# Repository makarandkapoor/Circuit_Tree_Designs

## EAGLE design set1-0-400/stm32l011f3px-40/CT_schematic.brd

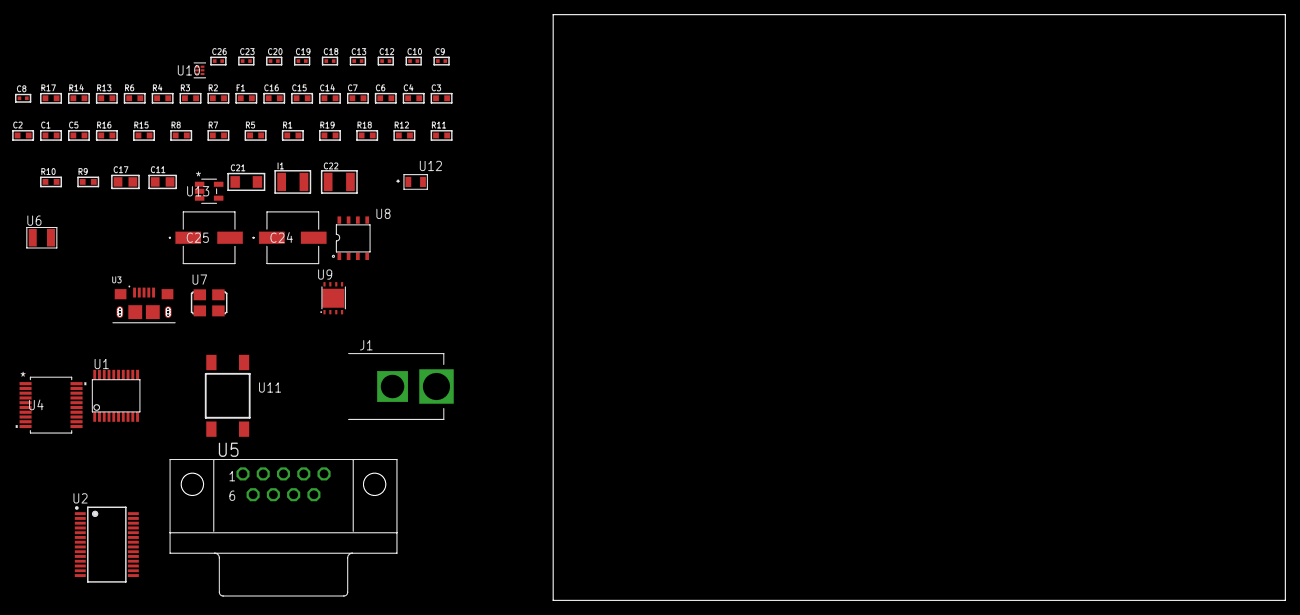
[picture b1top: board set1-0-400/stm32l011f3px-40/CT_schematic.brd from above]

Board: 2 copper layers, 61 parts (0 on the bottom side), 46 nets, no tracks yet.

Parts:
C1, C2, C3, C4: 1e-07; C0603
C5: 4.7e-06; C0603
C6: 1e-08; C0603
C7, C14, C15, C16: 1e-06; C0603
C8, C9: 1e-11; C0402
C10, C12, C13, C23: 1e-07; C0402
C11, C17: 4.7e-06; C0805
C18, C19, C20, C26: 1e-08; C0402
C21: 1e-05; C1206
C22: 1e-05; C1210
C24, C25: 0.0001; EXV-9H
F1: 240.0; L0603
I1: 1.5e-05; L1210
J1: PJ-037B; PJ-037B_PACKAGE
R1, R5, R7, R8, R15, R16: 10000.0; R0603
R2, R14: 1000.0; R0603
R3: 1600.5; R0603
R4, R6: 4700.0; R0603
R9, R10, R11, R12: 100000.0; R0603
R13: 2231.0; R0603
R17: 9100.0; R0603
R18: 680000.0; R0603
R19: 120000.0; R0603
U1: STM32L011F3P6; TSSOP20-I
U2: FT232RL-REEL; SSOP-28
U3: 10118193-0001LF; FCI_10118193-0001LF
U4: MAX3218EAP+T; SSOP-20
U5: 182-009-113R531; 182-009-MALE
U6: ABS07-32.768KHZ-7-T
U7: ASFL1-12MHZ-NCS; ASFL1
U8: idt74fct38072; IDT74FCT38072
U9: LP3878SDX-ADJ/NOPB; WSON-8
U10: TPS3895ADRYR; SON-6
U11: 4-1437565-2; SW_4-1437565-2
U12: Q65110A2395; LGM67K-G1J2-24-Z
U13: nc7sz125m5x; NC7SZ125M5X

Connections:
CLK_CRYSTAL_U1_2: C8.1, U1.2, U6.1
CLK_CRYSTAL_U1_3: C9.1, U1.3, U6.2
CLK_U1_6: U1.6, U8.7
CLK_U2_27: U2.27, U8.6
CLK_U8_3: U7.3, U8.3
GND: C1.2, C2.2, C3.2, C4.2, C5.2, C6.2, C7.2, C8.2, C9.2, C10.2, C11.2, C12.2, C13.2, C14.2, C15.2, C16.2, C18.2, C19.2, C20.2, C21.2, C22.2, C23.2, C24.2, C25.2, C26.2, J1.2, R2.2, R5.2, R8.2, R14.2, R17.2, R19.2, U1.15, U2.7, U2.18, U2.21, U2.25, U2.26, U3.5, U3.6, U3.7, U3.8, U3.9, U4.5, U4.17, U4.20, U5.5, U7.2, U8.4, U8.5, U8.8, U9.3, U9.PAD, U10.2, U12.C, U13.1, U13.3
NET_U1_1: R5.1, U1.1
NET_U1_4: R4.1, U1.4, U13.4
NET_U1_5: C6.1, C7.1, F1.1, U1.5
NET_U1_19: R3.1, U1.19, U12.A
NET_U1_20: R1.1, U1.20, U11.3, U11.4
NET_U2_14: R7.1, U2.14
NET_U2_17: C12.1, U2.17
NET_U2_19: R8.1, U2.19
NET_U3_1: R6.1, U3.1
NET_U3_2: U2.16, U3.2
NET_U3_3: U2.15, U3.3
NET_U4_1: I1.1, U4.1
NET_U4_2: R9.1, U4.2
NET_U4_3: R10.1, U4.3
NET_U4_4: R11.1, U4.4
NET_U4_15: C16.1, U4.15
NET_U4_16: C17.2, U4.16
NET_U4_18: C17.1, U4.18
NET_U4_19: C15.1, U4.19
NET_U5_2: U4.12, U5.2
NET_U5_3: U4.14, U5.3
NET_U5_7: U4.11, U5.7
NET_U5_8: U4.13, U5.8
NET_U9_1: C20.1, U9.1
NET_U9_6: R13.2, R14.1, U9.6
NET_U9_8: R12.1, U9.8
NET_U10_1: R16.1, R17.1, U10.1
NET_U10_3: R18.2, R19.1, U10.3
NET_U10_4: R15.1, U10.4, U13.2
NET_U11_1: R2.1, U11.1, U11.2
PROC_LPUART1_CTS: U1.12, U4.8
PROC_LPUART1_RTS: U1.14, U4.10
PROC_LPUART1_RX: U1.9, U4.9
PROC_LPUART1_TX: U1.8, U4.7
PROC_USART2_CTS: U1.13, U2.3
PROC_USART2_RTS: U1.7, U2.11
PROC_USART2_RX: U1.18, U2.1
PROC_USART2_TX: U1.17, U2.5
VCC_S1_10V1: C21.1, C24.1, C25.1, J1.1, R12.2, U9.4
VCC_TIER1_3V3: C1.1, C2.1, C3.1, C4.1, C5.1, C10.1, C11.1, C13.1, C14.1, C18.1, C19.1, C22.1, C23.1, C26.1, F1.2, I1.2, R1.2, R3.2, R4.2, R7.2, R9.2, R10.2, R11.2, R13.1, R15.2, R16.2, R18.1, U1.16, U2.4, U2.20, U4.6, U7.4, U8.1, U8.2, U9.5, U10.6, U13.5

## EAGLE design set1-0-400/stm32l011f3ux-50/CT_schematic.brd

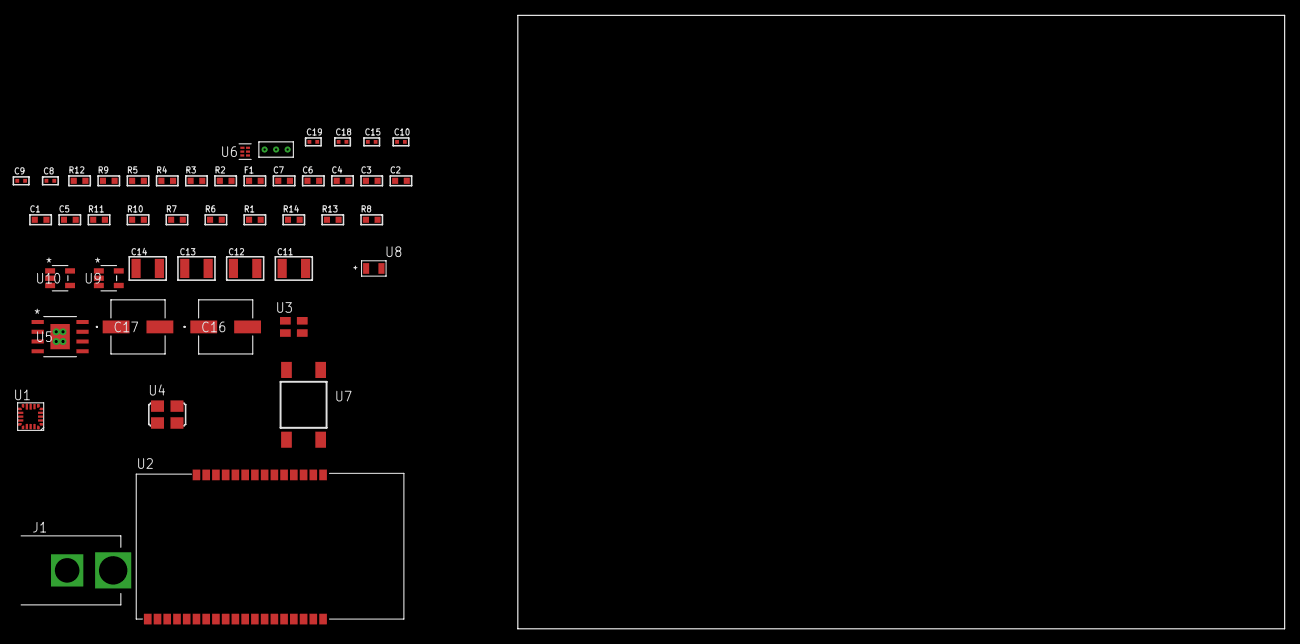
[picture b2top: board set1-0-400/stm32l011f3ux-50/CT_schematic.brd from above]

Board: 2 copper layers, 100.0 x 80.0 mm, 46 parts (0 on the bottom side), 21 nets, no tracks yet.

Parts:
C1, C2, C3, C4: 1e-07; C0603
C5: 4.7e-06; C0603
C6: 1e-08; C0603
C7: 1e-06; C0603
C8, C15: 1e-07; C0402
C9, C10, C18, C19: 1e-08; C0402
C11, C12, C13, C14: 1e-05; C1210
C16, C17: 0.0001; EXV-9H
F1: 240.0; L0603
J1: PJ-037B; PJ-037B_PACKAGE
R1, R6, R7, R10, R11: 10000.0; R0603
R2: 1000.0; R0603
R3: 1600.5; R0603
R4, R5: 4700.0; R0603
R8: 4031.5447154472; R0603
R9: 2200.0; R0603
R12: 9100.0; R0603
R13: 680000.0; R0603
R14: 120000.0; R0603
U1: STM32L011F3U6TR; UFQFPN20
U2: ETRX3587
U3: ASEK-32.768KHz-ECST; ASEK
U4: ASFL1-12MHZ-NCS; ASFL1
U5: MIC5234YME; SOIC-8_EP
U6: TPS3895ADRYR; SON-6
U7: 4-1437565-2; SW_4-1437565-2
U8: Q65110A2395; LGM67K-G1J2-24-Z
U9, U10: nc7sz125m5x; NC7SZ125M5X
U11: Dummy; DUMMY_PACKAGE_92

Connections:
CLK_U1_1: U1.1, U3.3
CLK_U1_5: U1.5, U4.3
GND: C1.2, C2.2, C3.2, C4.2, C5.2, C6.2, C7.2, C8.2, C9.2, C10.2, C11.2, C12.2, C13.2, C14.2, C15.2, C16.2, C17.2, C18.2, C19.2, J1.2, R2.2, R6.2, R7.2, R9.2, R12.2, R14.2, U1.12, U2.1, U2.13, U2.19, U2.20, U2.31, U2.33, U3.2, U4.2, U5.7, U5.EPAD, U6.2, U8.C, U9.1, U9.3, U10.1, U10.3, U11.1
NET_U1_3: R5.1, U1.3, U10.4
NET_U1_4: C6.1, C7.1, F1.1, U1.4
NET_U1_19: R3.1, U1.19, U8.A
NET_U1_20: R1.1, R6.1, U1.20, U7.3, U7.4
NET_U2_7: R4.1, U2.7, U9.4
NET_U2_21: R7.1, U2.21
NET_U5_4: R8.2, R9.1, U5.4
NET_U6_1: R11.1, R12.1, U6.1
NET_U6_3: R13.2, R14.1, U6.3
NET_U6_4: R10.1, U6.4, U9.2, U10.2
NET_U7_1: R2.1, U7.1, U7.2
PROC_LPUART1_CTS: U1.9, U2.8
PROC_LPUART1_RTS: U1.11, U2.6
PROC_LPUART1_RX: U1.16, U2.17
PROC_LPUART1_TX: U1.6, U2.18
PROC_TIM2_CH3: U1.15, U11.2, U11.3
VCC_S1_15V6: C11.1, C12.1, C16.1, C17.1, J1.1, U5.5, U5.8
VCC_TIER1_3V3: C1.1, C2.1, C3.1, C4.1, C5.1, C8.1, C9.1, C10.1, C13.1, C14.1, C15.1, C18.1, C19.1, F1.2, R1.2, R3.2, R4.2, R5.2, R8.1, R10.2, R11.2, R13.1, U1.13, U2.32, U3.4, U4.4, U5.1, U6.6, U9.5, U10.5

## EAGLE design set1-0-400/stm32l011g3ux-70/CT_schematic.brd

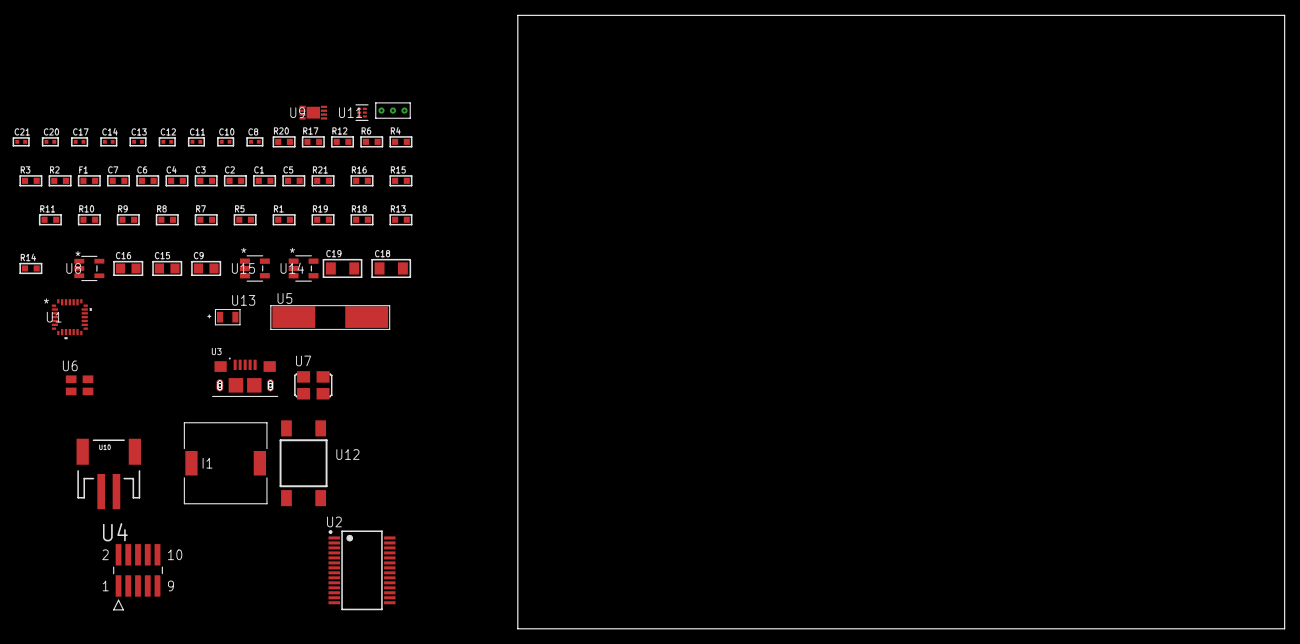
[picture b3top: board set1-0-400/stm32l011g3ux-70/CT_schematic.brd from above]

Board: 2 copper layers, 60 parts (0 on the bottom side), 37 nets, no tracks yet.

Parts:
C1, C2, C3, C4: 1e-07; C0603
C5: 4.7e-06; C0603
C6: 1e-08; C0603
C7: 1e-06; C0603
C8, C10, C11, C12, C17: 1e-07; C0402
C9: 4.7e-06; C0805
C13, C14, C20, C21: 1e-08; C0402
C15, C16: 1e-05; C0805
C18, C19: 1e-05; C1206
F1: 240.0; L0603
I1: 2.5e-06; DR1040
R1, R5, R7, R8, R9, R10, R11, R15, R16, R21: 10000.0; R0603
R2: 1000.0; R0603
R3: 1600.5; R0603
R4, R6: 4700.0; R0603
R12: 5.0; R0603
R13: 220000.0; R0603
R14: 1000000.0; R0603
R17: 9100.0; R0603
R18: 680000.0; R0603
R19: 120000.0; R0603
R20: 2000.0; R0603
U1: STM32L011G3U6; UFQFPN28
U2: FT232RL-REEL; SSOP-28
U3: 10118193-0001LF; FCI_10118193-0001LF
U4: FTSH-105-01-L-DV-K; SAMTEC_FTSH-105-01-L-DV-K
U5: ABLS-12.000MHZ-B4-T
U6: ASEK-32.768KHz-ECST; ASEK
U7: ASFL1-12MHZ-NCS; ASFL1
U8: ltc3406es5; TSOT-23-5
U9: MCP73831T-2ACI/MC; DFN8_2X3MC
U10: S2B-PH-SM4-TB(LF)(SN); JST-2-SMD
U11: TPS3895ADRYR; SON-6
U12: 4-1437565-2; SW_4-1437565-2
U13: Q65110A2395; LGM67K-G1J2-24-Z
U14, U15: nc7sz125m5x; NC7SZ125M5X
U16: Dummy; DUMMY_PACKAGE_125

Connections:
CLK_CRYSTAL_U2_27: U2.27, U5.1
CLK_CRYSTAL_U2_28: U2.28, U5.2
CLK_U1_2: U1.2, U6.3
CLK_U1_6: U1.6, U7.3
GND: C1.2, C2.2, C3.2, C4.2, C5.2, C6.2, C7.2, C8.2, C9.2, C10.2, C11.2, C12.2, C13.2, C14.2, C15.2, C16.1, C16.2, C17.2, C18.2, C19.2, C20.2, C21.2, R2.2, R5.2, R8.2, R12.2, R13.2, R17.2, R19.2, R20.2, U1.16, U2.7, U2.18, U2.21, U2.25, U2.26, U3.5, U3.6, U3.7, U3.8, U3.9, U4.3, U4.5, U6.2, U7.2, U8.2, U9.6, U9.9, U10.2, U11.2, U13.C, U14.2, U14.3, U15.1, U15.3, U16.1
INPUT_USBPOWER_5V: C18.1, R6.1, R21.2, U3.1, U9.1, U9.2
NET_U1_1: R5.1, U1.1
NET_U1_4: R4.1, U1.4, U15.4
NET_U1_5: C6.1, C7.1, F1.1, U1.5
NET_U1_27: R3.1, U1.27, U13.A
NET_U1_28: R1.1, U1.28, U12.3, U12.4
NET_U2_14: R7.1, U2.14
NET_U2_17: C10.1, U2.17
NET_U2_19: R8.1, U2.19
NET_U3_2: U2.16, U3.2
NET_U3_3: U2.15, U3.3
NET_U4_9: R12.1, U4.9
NET_U8_3: I1.1, U8.3
NET_U8_5: R13.1, R14.1, U8.5
NET_U8_ATNET_3: I1.2, R14.2
NET_U9_5: R21.1, U9.5
NET_U9_8: R20.1, U9.8
NET_U11_1: R16.1, R17.1, U11.1
NET_U11_3: R18.2, R19.1, U11.3
NET_U11_4: R15.1, U11.4, U14.4, U15.2
NET_U12_1: R2.1, U12.1, U12.2
PROC_ADC_IN4: U1.10, U16.2
PROC_ADC_IN7: U1.13, U16.3
PROC_LPUART1_CTS: U1.12, U2.3
PROC_LPUART1_RTS: U1.15, U2.11
PROC_LPUART1_RX: U1.9, U2.1
PROC_LPUART1_TX: U1.7, U2.5
PROC_SYS_SWCLK: R10.1, U1.22, U4.4
PROC_SYS_SWDIO: R11.1, U1.21, U4.2
RST_OUT_U4_JTAG_RST_B: R9.1, U4.10, U14.1
VCC_S1_3V7: C15.1, C19.1, U8.4, U9.3, U9.4, U10.1
VCC_TIER1_3V3: C1.1, C2.1, C3.1, C4.1, C5.1, C8.1, C9.1, C11.1, C12.1, C13.1, C14.1, C16.2, C17.1, C20.1, C21.1, F1.2, I1.2, R1.2, R3.2, R4.2, R7.2, R9.2, R10.2, R11.2, R14.2, R15.2, R16.2, R18.1, U1.17, U2.4, U2.20, U4.1, U6.4, U7.4, U11.6, U14.5, U15.5

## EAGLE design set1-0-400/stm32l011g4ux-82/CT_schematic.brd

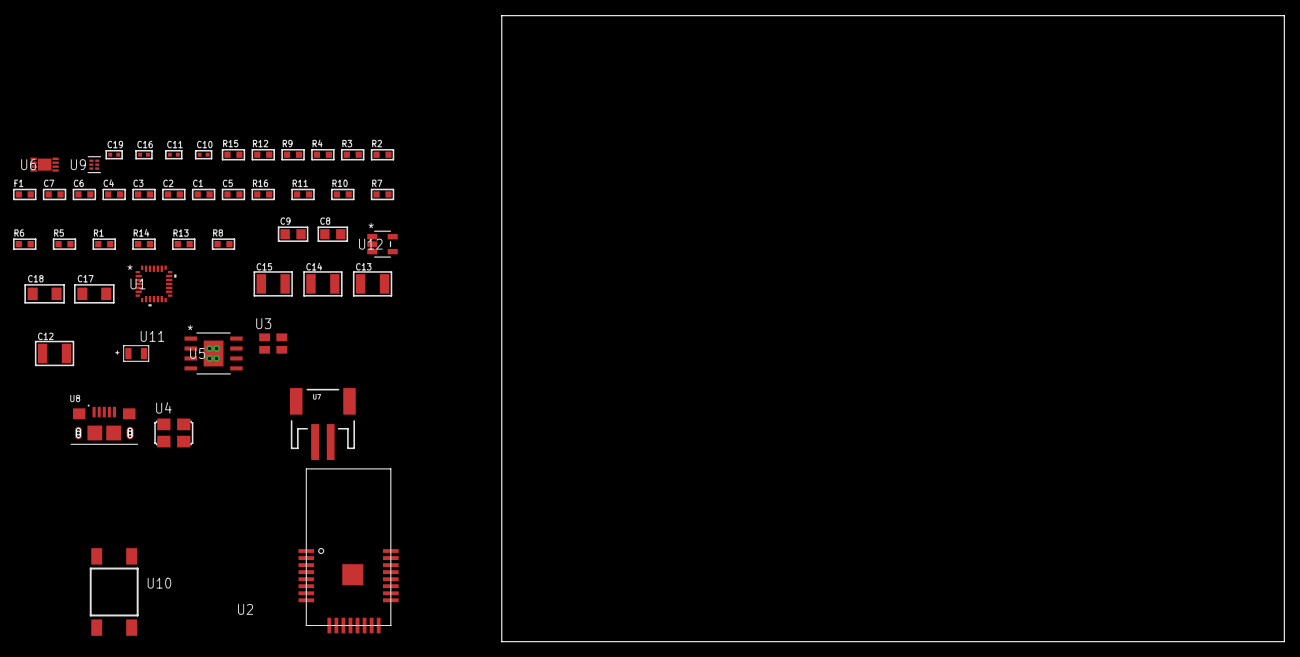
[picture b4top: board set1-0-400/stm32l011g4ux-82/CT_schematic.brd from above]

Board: 2 copper layers, 154.3 x 80.0 mm, 48 parts (0 on the bottom side), 24 nets, no tracks yet.

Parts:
C1, C2, C3, C4: 1e-07; C0603
C5: 4.7e-06; C0603
C6: 1e-08; C0603
C7: 1e-06; C0603
C8, C9: 1e-05; C0805
C10, C11, C19: 1e-08; C0402
C12, C13, C14, C15: 1e-05; C1210
C16: 1e-07; C0402
C17, C18: 1e-05; C1206
F1: 240.0; L0603
R1, R5, R6, R7, R10, R11, R16: 10000.0; R0603
R2: 1000.0; R0603
R3: 1600.5; R0603
R4: 4700.0; R0603
R8: 4031.5447154472; R0603
R9: 2200.0; R0603
R12: 9100.0; R0603
R13: 680000.0; R0603
R14: 120000.0; R0603
R15: 2000.0; R0603
U1: STM32L011G4U6; UFQFPN28
U2: ATBTLC1000-MR110CA
U3: ASEK-32.768KHz-ECST; ASEK
U4: ASFL1-12MHZ-NCS; ASFL1
U5: MIC5234YME; SOIC-8_EP
U6: MCP73831T-2ACI/MC; DFN8_2X3MC
U7: S2B-PH-SM4-TB(LF)(SN); JST-2-SMD
U8: 10118193-0001LF; FCI_10118193-0001LF
U9: TPS3895ADRYR; SON-6
U10: 4-1437565-2; SW_4-1437565-2
U11: Q65110A2395; LGM67K-G1J2-24-Z
U12: nc7sz125m5x; NC7SZ125M5X

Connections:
CLK_U1_2: U1.2, U3.3
CLK_U1_6: U1.6, U4.3
GND: C1.2, C2.2, C3.2, C4.2, C5.2, C6.2, C7.2, C8.2, C9.2, C10.2, C11.2, C12.2, C13.2, C14.2, C15.2, C16.2, C17.2, C18.2, C19.2, R2.2, R5.2, R9.2, R12.2, R14.2, R15.2, U1.16, U2.1, U2.9, U2.13, U2.24, U2.25, U3.2, U4.2, U5.7, U5.EPAD, U6.6, U6.9, U7.2, U8.5, U8.6, U8.7, U8.8, U8.9, U9.2, U11.C, U12.1, U12.3
INPUT_USBPOWER_5V: C17.1, R16.2, U6.1, U6.2, U8.1
NET_U1_1: R5.1, U1.1
NET_U1_4: R4.1, U1.4, U12.4
NET_U1_5: C6.1, C7.1, F1.1, U1.5
NET_U1_27: R3.1, U1.27, U11.A
NET_U1_28: R1.1, U1.28, U10.3, U10.4
NET_U2_17: R6.1, U2.17
NET_U2_20: R7.1, U2.20
NET_U5_4: R8.2, R9.1, U5.4
NET_U6_5: R16.1, U6.5
NET_U6_8: R15.1, U6.8
NET_U9_1: R11.1, R12.1, U9.1
NET_U9_3: R13.2, R14.1, U9.3
NET_U9_4: R10.1, U9.4, U12.2
NET_U10_1: R2.1, U10.1, U10.2
PROC_SPI1_MISO: U1.12, U2.14
PROC_SPI1_MOSI: U1.13, U2.11
PROC_SPI1_NSS: U1.10, U2.12
PROC_SPI1_SCK: U1.11, U2.10
VCC_S1_3V7: C12.1, C13.1, C18.1, U5.5, U5.8, U6.3, U6.4, U7.1
VCC_TIER1_3V3: C1.1, C2.1, C3.1, C4.1, C5.1, C8.1, C9.1, C10.1, C11.1, C14.1, C15.1, C16.1, C19.1, F1.2, R1.2, R3.2, R4.2, R6.2, R7.2, R8.1, R10.2, R11.2, R13.1, U1.17, U2.6, U2.22, U3.4, U4.4, U5.1, U9.6, U12.5

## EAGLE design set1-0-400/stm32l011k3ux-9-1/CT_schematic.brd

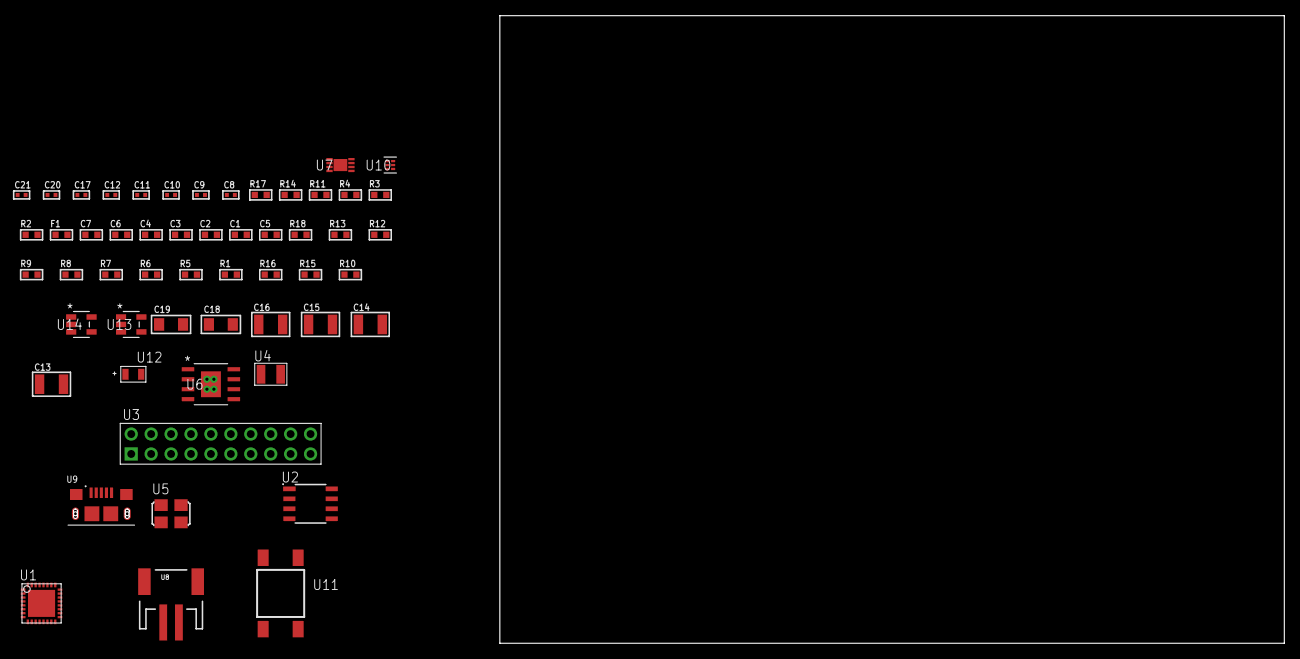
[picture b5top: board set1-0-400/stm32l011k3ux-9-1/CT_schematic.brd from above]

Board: 2 copper layers, 154.3 x 80.0 mm, 54 parts (0 on the bottom side), 27 nets, no tracks yet.

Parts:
C1, C2, C3, C4: 1e-07; C0603
C5: 4.7e-06; C0603
C6: 1e-08; C0603
C7: 1e-06; C0603
C8, C9: 1e-11; C0402
C10, C12, C20, C21: 1e-08; C0402
C11, C17: 1e-07; C0402
C13, C14, C15, C16: 1e-05; C1210
C18, C19: 1e-05; C1206
F1: 240.0; L0603
R1, R5, R6, R7, R8, R9, R12, R13, R18: 10000.0; R0603
R2: 1000.0; R0603
R3: 1600.5; R0603
R4: 4700.0; R0603
R10: 4031.5447154472; R0603
R11: 2200.0; R0603
R14: 9100.0; R0603
R15: 680000.0; R0603
R16: 120000.0; R0603
R17: 2000.0; R0603
U1: STM32L011K3U6; UFQFPN32
U2: AT25256B-SSHL-T; SOIC-8
U3: TST-110-05-T-D-RA
U4: ABS07-32.768KHZ-7-T
U5: ASFL1-12MHZ-NCS; ASFL1
U6: MIC5234YME; SOIC-8_EP
U7: MCP73831T-2ACI/MC; DFN8_2X3MC
U8: S2B-PH-SM4-TB(LF)(SN); JST-2-SMD
U9: 10118193-0001LF; FCI_10118193-0001LF
U10: TPS3895ADRYR; SON-6
U11: 4-1437565-2; SW_4-1437565-2
U12: Q65110A2395; LGM67K-G1J2-24-Z
U13, U14: nc7sz125m5x; NC7SZ125M5X

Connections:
CLK_CRYSTAL_U1_2: C8.1, U1.2, U4.1
CLK_CRYSTAL_U1_3: C9.1, U1.3, U4.2
CLK_U1_6: U1.6, U5.3
GND: C1.2, C2.2, C3.2, C4.2, C5.2, C6.2, C7.2, C8.2, C9.2, C10.2, C11.2, C12.2, C13.2, C14.2, C15.2, C16.2, C17.2, C18.2, C19.2, C20.2, C21.2, R2.2, R5.2, R11.2, R14.2, R16.2, R17.2, U1.EPAD, U2.4, U3.4, U3.6, U3.8, U3.10, U3.12, U3.14, U3.16, U3.18, U3.20, U5.2, U6.7, U6.EPAD, U7.6, U7.9, U8.2, U9.5, U9.6, U9.7, U9.8, U9.9, U10.2, U12.C, U13.2, U13.3, U14.1, U14.3
INPUT_USBPOWER_5V: C18.1, R18.2, U7.1, U7.2, U9.1
NET_U1_4: R4.1, U1.4, U14.4
NET_U1_5: C6.1, C7.1, F1.1, U1.5
NET_U1_31: R3.1, R5.1, U1.31, U12.A
NET_U1_32: R1.1, U1.32, U11.3, U11.4
NET_U2_3: R6.1, U2.3
NET_U2_7: R8.1, U2.7
NET_U6_4: R10.2, R11.1, U6.4
NET_U7_5: R18.1, U7.5
NET_U7_8: R17.1, U7.8
NET_U10_1: R13.1, R14.1, U10.1
NET_U10_3: R15.2, R16.1, U10.3
NET_U10_4: R12.1, U10.4, U13.4, U14.2
NET_U11_1: R2.1, U11.1, U11.2
PROC_SPI1_MISO: U1.12, U2.2
PROC_SPI1_MOSI: U1.13, U2.5
PROC_SPI1_NSS: R7.1, U1.10, U2.1
PROC_SPI1_SCK: U1.11, U2.6
PROC_SYS_SWCLK: U1.24, U3.9
PROC_SYS_SWDIO: U1.23, U3.7
RST_OUT_U3_SRESET_B: R9.1, U3.15, U13.1
VCC_S1_3V7: C13.1, C14.1, C19.1, U6.5, U6.8, U7.3, U7.4, U8.1
VCC_TIER1_3V3: C1.1, C2.1, C3.1, C4.1, C5.1, C10.1, C11.1, C12.1, C15.1, C16.1, C17.1, C20.1, C21.1, F1.2, R1.2, R3.2, R4.2, R6.2, R7.2, R8.2, R9.2, R10.1, R12.2, R13.2, R15.1, U1.1, U1.17, U2.8, U3.1, U5.4, U6.1, U10.6, U13.5, U14.5

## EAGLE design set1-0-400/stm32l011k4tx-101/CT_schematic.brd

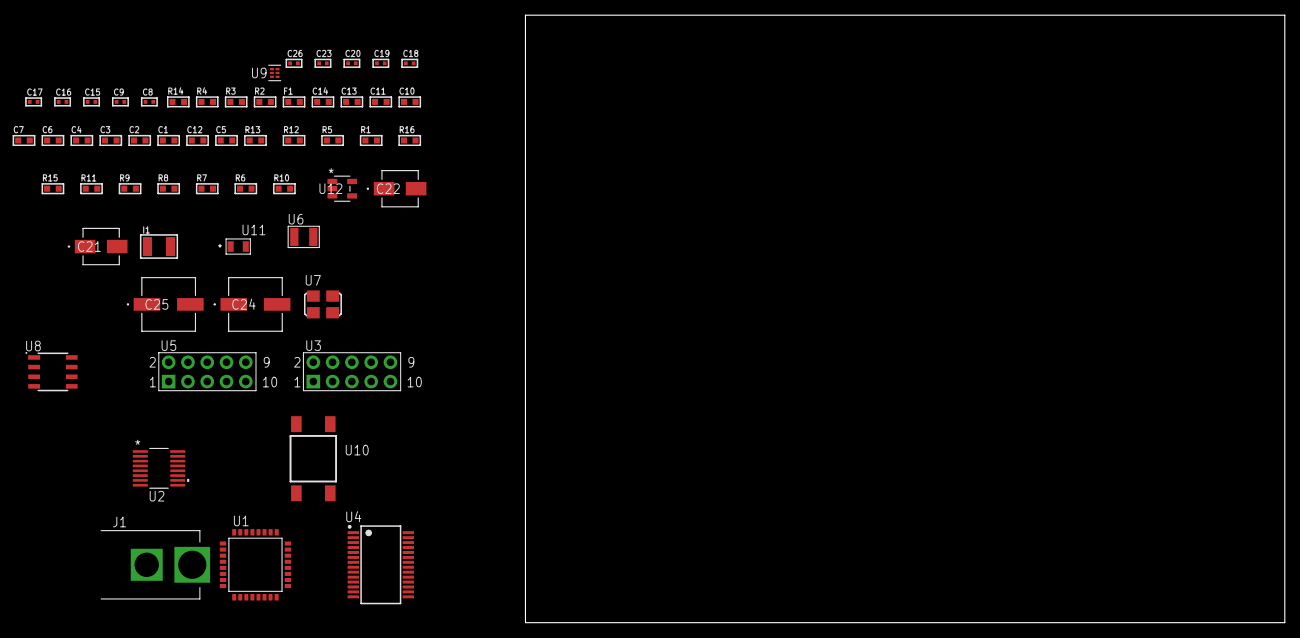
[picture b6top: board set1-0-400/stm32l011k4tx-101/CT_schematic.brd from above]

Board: 2 copper layers, 100.0 x 80.0 mm, 57 parts (0 on the bottom side), 45 nets, no tracks yet.

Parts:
C1, C2, C3, C4: 1e-07; C0603
C5: 4.7e-06; C0603
C6: 1e-08; C0603
C7, C10, C11, C13, C14: 1e-06; C0603
C8, C9: 1e-11; C0402
C12: 2.2e-07; C0603
C15, C16, C17, C18, C19, C23: 1e-07; C0402
C20, C26: 1e-08; C0402
C21: 1e-06; EXV-9B
C22: 2.2e-06; EXV-9B
C24, C25: 0.0001; EXV-9H
F1: 240.0; L0603
I1: 1e-05; L1210
J1: PJ-037B; PJ-037B_PACKAGE
R1, R5, R12, R13: 10000.0; R0603
R2: 1000.0; R0603
R3: 1600.5; R0603
R4: 4700.0; R0603
R6, R7, R8, R9, R11: 100000.0; R0603
R10: 164658.62; R0603
R14: 9100.0; R0603
R15: 680000.0; R0603
R16: 120000.0; R0603
U1: STM32L011K4T6; LQFP32
U2: LTC2804CGN-1#PBF; SSOP-16
U3, U5: HTSS-105-01-G-D
U4: ST3241EBPR; SSOP-28
U6: ABS07-32.768KHZ-7-T
U7: ASFL1-12MHZ-NCS; ASFL1
U8: LP2954AIMX/NOPB; LP2954
U9: TPS3895ADRYR; SON-6
U10: 4-1437565-2; SW_4-1437565-2
U11: Q65110A2395; LGM67K-G1J2-24-Z
U12: nc7sz125m5x; NC7SZ125M5X

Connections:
CLK_CRYSTAL_U1_2: C8.1, U1.2, U6.1
CLK_CRYSTAL_U1_3: C9.1, U1.3, U6.2
CLK_U1_6: U1.6, U7.3
GND: C1.2, C2.2, C3.2, C4.2, C5.2, C6.2, C7.2, C8.2, C9.2, C10.2, C11.2, C13.2, C14.2, C15.2, C18.2, C19.2, C20.2, C21.2, C22.2, C23.2, C24.2, C25.2, C26.2, J1.2, R2.2, R5.2, R11.2, R14.2, R16.2, U1.16, U1.32, U2.8, U3.9, U4.23, U4.25, U5.9, U7.2, U8.4, U9.2, U11.C, U12.1, U12.3
NET_U1_4: R4.1, U1.4, U12.4
NET_U1_5: C6.1, C7.1, F1.1, U1.5
NET_U1_30: R3.1, U1.30, U11.A
NET_U1_31: R1.1, R5.1, U1.31, U10.3, U10.4
NET_U2_6: C10.1, U2.6
NET_U2_7: C12.1, I1.2, U2.7
NET_U2_9: C11.1, U2.9
NET_U2_10: C12.2, U2.10
NET_U2_11: R6.1, U2.11
NET_U3_3: U2.1, U3.3
NET_U3_4: U2.2, U3.4
NET_U3_5: U2.3, U3.5
NET_U3_6: U2.4, U3.6
NET_U4_1: C17.1, U4.1
NET_U4_2: C17.2, U4.2
NET_U4_3: C19.1, U4.3
NET_U4_22: R7.1, U4.22
NET_U4_24: C16.2, U4.24
NET_U4_27: C18.1, U4.27
NET_U4_28: C16.1, U4.28
NET_U5_3: U4.4, U5.3
NET_U5_4: U4.5, U5.4
NET_U5_5: U4.9, U5.5
NET_U5_6: U4.10, U5.6
NET_U8_3: R9.1, U8.3
NET_U8_5: R8.1, U8.5
NET_U8_7: R10.2, R11.1, U8.7
NET_U9_1: R13.1, R14.1, U9.1
NET_U9_3: R15.2, R16.1, U9.3
NET_U9_4: R12.1, U9.4, U12.2
NET_U10_1: R2.1, U10.1, U10.2
PROC_LPUART1_CTS: U1.12, U2.13
PROC_LPUART1_RTS: U1.15, U2.15
PROC_LPUART1_RX: U1.9, U2.16
PROC_LPUART1_TX: U1.7, U2.14
PROC_USART2_CTS: U1.13, U4.13
PROC_USART2_RTS: U1.14, U4.18
PROC_USART2_RX: U1.20, U4.19
PROC_USART2_TX: U1.8, U4.14
VCC_S1_15V0: C21.1, C24.1, C25.1, J1.1, R9.2, U8.8
VCC_TIER1_3V3: C1.1, C2.1, C3.1, C4.1, C5.1, C13.1, C14.1, C15.1, C20.1, C22.1, C23.1, C26.1, F1.2, I1.1, R1.2, R3.2, R4.2, R6.2, R7.2, R8.2, R10.1, R12.2, R13.2, R15.1, U1.1, U1.17, U2.5, U2.12, U4.26, U7.4, U8.1, U9.6, U12.5

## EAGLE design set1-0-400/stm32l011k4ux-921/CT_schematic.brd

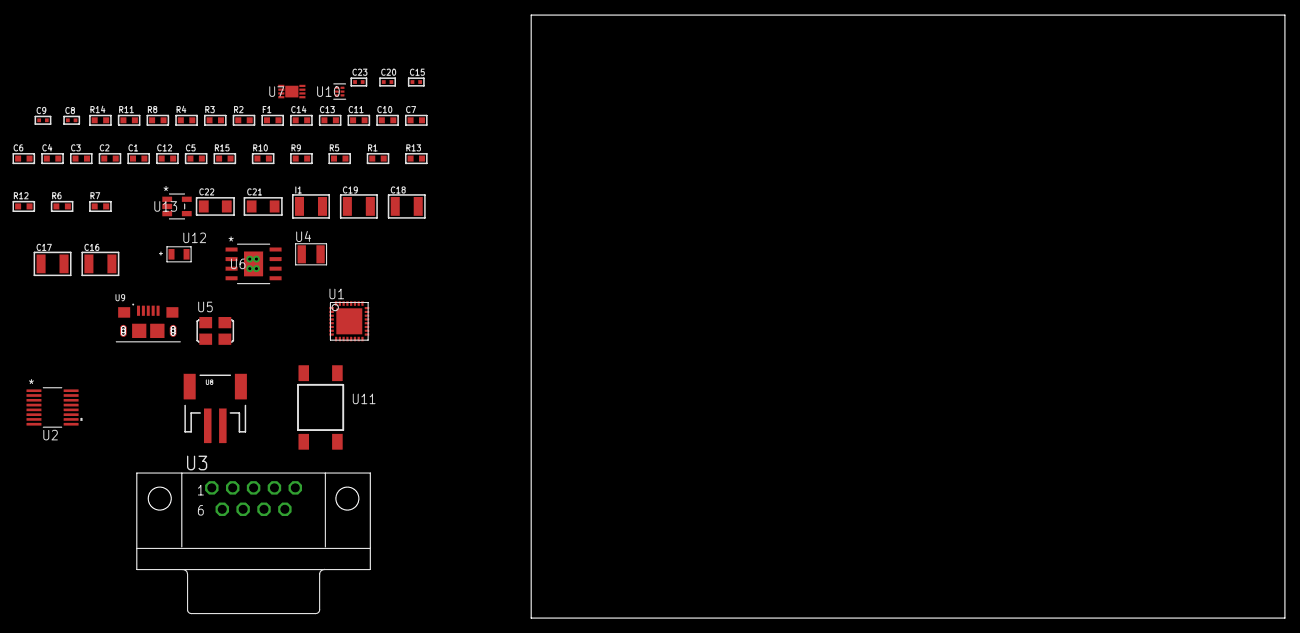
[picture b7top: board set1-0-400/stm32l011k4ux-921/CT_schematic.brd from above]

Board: 2 copper layers, 53 parts (0 on the bottom side), 31 nets, no tracks yet.

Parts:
C1, C2, C3, C4: 1e-07; C0603
C5: 4.7e-06; C0603
C6: 1e-08; C0603
C7, C10, C11, C13, C14: 1e-06; C0603
C8, C9: 1e-11; C0402
C12: 2.2e-07; C0603
C15, C23: 1e-08; C0402
C16, C17, C18, C19: 1e-05; C1210
C20: 1e-07; C0402
C21, C22: 1e-05; C1206
F1: 240.0; L0603
I1: 1e-05; L1210
R1, R5, R9, R10, R15: 10000.0; R0603
R2: 1000.0; R0603
R3: 1600.5; R0603
R4: 4700.0; R0603
R6: 100000.0; R0603
R7: 4031.5447154472; R0603
R8: 2200.0; R0603
R11: 9100.0; R0603
R12: 680000.0; R0603
R13: 120000.0; R0603
R14: 2000.0; R0603
U1: STM32L011K4U3; UFQFPN32
U2: LTC2804CGN-1#PBF; SSOP-16
U3: 182-009-113R531; 182-009-MALE
U4: ABS07-32.768KHZ-7-T
U5: ASFL1-12MHZ-NCS; ASFL1
U6: MIC5234YME; SOIC-8_EP
U7: MCP73831T-2ACI/MC; DFN8_2X3MC
U8: S2B-PH-SM4-TB(LF)(SN); JST-2-SMD
U9: 10118193-0001LF; FCI_10118193-0001LF
U10: TPS3895ADRYR; SON-6
U11: 4-1437565-2; SW_4-1437565-2
U12: Q65110A2395; LGM67K-G1J2-24-Z
U13: nc7sz125m5x; NC7SZ125M5X

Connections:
CLK_CRYSTAL_U1_2: C8.1, U1.2, U4.1
CLK_CRYSTAL_U1_3: C9.1, U1.3, U4.2
CLK_U1_6: U1.6, U5.3
GND: C1.2, C2.2, C3.2, C4.2, C5.2, C6.2, C7.2, C8.2, C9.2, C10.2, C11.2, C13.2, C14.2, C15.2, C16.2, C17.2, C18.2, C19.2, C20.2, C21.2, C22.2, C23.2, R2.2, R5.2, R8.2, R11.2, R13.2, R14.2, U1.EPAD, U2.8, U3.5, U5.2, U6.7, U6.EPAD, U7.6, U7.9, U8.2, U9.5, U9.6, U9.7, U9.8, U9.9, U10.2, U12.C, U13.1, U13.3
INPUT_USBPOWER_5V: C21.1, R15.2, U7.1, U7.2, U9.1
NET_U1_4: R4.1, U1.4, U13.4
NET_U1_5: C6.1, C7.1, F1.1, U1.5
NET_U1_31: R3.1, R5.1, U1.31, U12.A
NET_U1_32: R1.1, U1.32, U11.3, U11.4
NET_U2_6: C10.1, U2.6
NET_U2_7: C12.1, I1.2, U2.7
NET_U2_9: C11.1, U2.9
NET_U2_10: C12.2, U2.10
NET_U2_11: R6.1, U2.11
NET_U3_2: U2.1, U3.2
NET_U3_3: U2.3, U3.3
NET_U3_7: U2.2, U3.7
NET_U3_8: U2.4, U3.8
NET_U6_4: R7.2, R8.1, U6.4
NET_U7_5: R15.1, U7.5
NET_U7_8: R14.1, U7.8
NET_U10_1: R10.1, R11.1, U10.1
NET_U10_3: R12.2, R13.1, U10.3
NET_U10_4: R9.1, U10.4, U13.2
NET_U11_1: R2.1, U11.1, U11.2
PROC_LPUART1_CTS: U1.12, U2.13
PROC_LPUART1_RTS: U1.15, U2.15
PROC_LPUART1_RX: U1.9, U2.16
PROC_LPUART1_TX: U1.7, U2.14
VCC_S1_3V7: C16.1, C17.1, C22.1, U6.5, U6.8, U7.3, U7.4, U8.1
VCC_TIER1_3V3: C1.1, C2.1, C3.1, C4.1, C5.1, C13.1, C14.1, C15.1, C18.1, C19.1, C20.1, C23.1, F1.2, I1.1, R1.2, R3.2, R4.2, R6.2, R7.1, R9.2, R10.2, R12.1, U1.1, U1.17, U2.5, U2.12, U5.4, U6.1, U10.6, U13.5

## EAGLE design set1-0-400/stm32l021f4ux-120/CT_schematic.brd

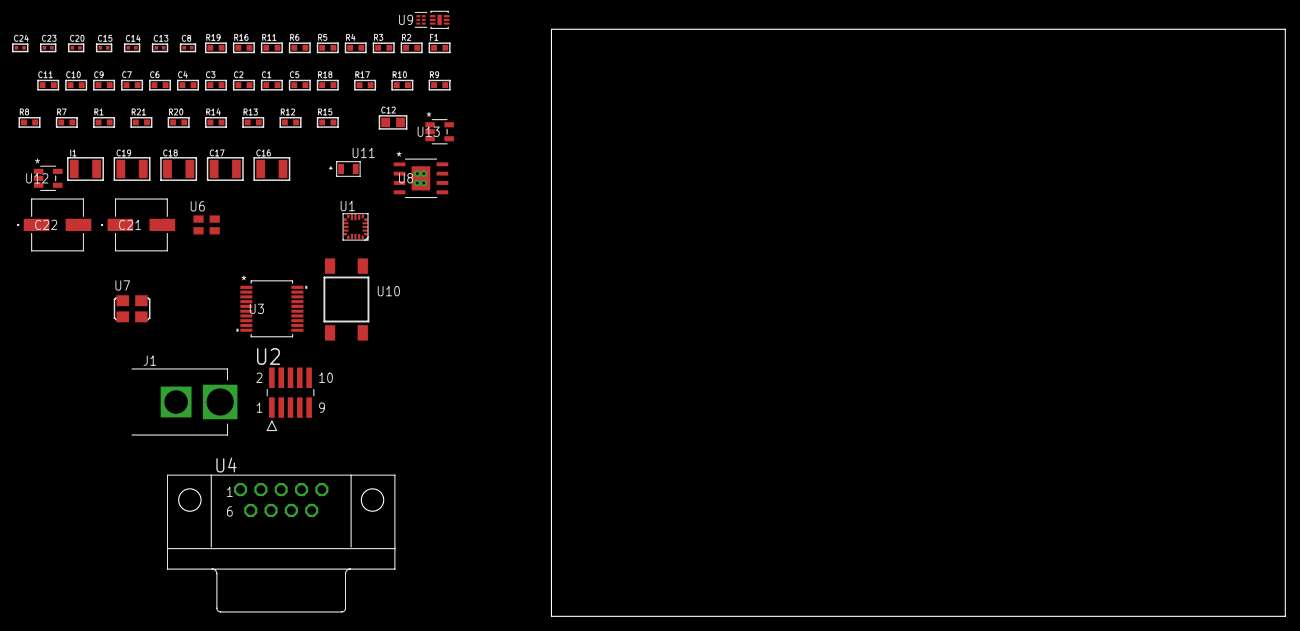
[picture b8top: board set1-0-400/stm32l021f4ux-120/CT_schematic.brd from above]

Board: 2 copper layers, 100.0 x 80.0 mm, 61 parts (0 on the bottom side), 36 nets, no tracks yet.

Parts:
C1, C2, C3, C4: 1e-07; C0603
C5: 4.7e-06; C0603
C6: 1e-08; C0603
C7, C9, C10, C11: 1e-06; C0603
C8, C13, C20: 1e-07; C0402
C12: 4.7e-06; C0805
C14, C15, C23, C24: 1e-08; C0402
C16, C17, C18, C19: 1e-05; C1210
C21, C22: 0.0001; EXV-9H
F1: 240.0; L0603
I1: 1.5e-05; L1210
J1: PJ-037B; PJ-037B_PACKAGE
R1, R7, R8, R9, R10, R17, R18: 10000.0; R0603
R2: 1000.0; R0603
R3: 1600.5; R0603
R4: 4700.0; R0603
R5, R6, R16: 2200.0; R0603
R11: 5.0; R0603
R12, R13, R14: 100000.0; R0603
R15: 4031.5447154472; R0603
R19: 9100.0; R0603
R20: 680000.0; R0603
R21: 120000.0; R0603
U1: STM32L021F4U6TR; UFQFPN20
U2: FTSH-105-01-L-DV-K; SAMTEC_FTSH-105-01-L-DV-K
U3: MAX3218EAP+T; SSOP-20
U4: 182-009-113R531; 182-009-MALE
U5: SI7006-A20-IM; DFN-6
U6: ASEK-32.768KHz-ECST; ASEK
U7: ASFL1-12MHZ-NCS; ASFL1
U8: MIC5234YME; SOIC-8_EP
U9: TPS3895ADRYR; SON-6
U10: 4-1437565-2; SW_4-1437565-2
U11: Q65110A2395; LGM67K-G1J2-24-Z
U12, U13: nc7sz125m5x; NC7SZ125M5X

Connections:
CLK_U1_1: U1.1, U6.3
CLK_U1_5: U1.5, U7.3
GND: C1.2, C2.2, C3.2, C4.2, C5.2, C6.2, C7.2, C8.2, C9.2, C10.2, C11.2, C13.2, C14.2, C15.2, C16.2, C17.2, C18.2, C19.2, C20.2, C21.2, C22.2, C23.2, C24.2, J1.2, R2.2, R7.2, R11.2, R16.2, R19.2, R21.2, U1.12, U2.3, U2.5, U3.5, U3.17, U3.20, U4.5, U5.2, U5.7, U6.2, U7.2, U8.7, U8.EPAD, U9.2, U11.C, U12.2, U12.3, U13.1, U13.3
NET_U1_3: R4.1, U1.3, U13.4
NET_U1_4: C6.1, C7.1, F1.1, U1.4
NET_U1_7: R5.1, U1.7, U5.6
NET_U1_15: R6.1, U1.15, U5.1
NET_U1_18: R3.1, U1.18, U11.A
NET_U1_20: R1.1, R7.1, U1.20, U10.3, U10.4
NET_U2_9: R11.1, U2.9
NET_U3_1: I1.1, U3.1
NET_U3_2: R12.1, U3.2
NET_U3_3: R13.1, U3.3
NET_U3_4: R14.1, U3.4
NET_U3_15: C11.1, U3.15
NET_U3_16: C12.2, U3.16
NET_U3_18: C12.1, U3.18
NET_U3_19: C10.1, U3.19
NET_U4_2: U3.12, U4.2
NET_U4_3: U3.14, U4.3
NET_U4_7: U3.11, U4.7
NET_U4_8: U3.13, U4.8
NET_U8_4: R15.2, R16.1, U8.4
NET_U9_1: R18.1, R19.1, U9.1
NET_U9_3: R20.2, R21.1, U9.3
NET_U9_4: R17.1, U9.4, U12.4, U13.2
NET_U10_1: R2.1, U10.1, U10.2
PROC_LPUART1_CTS: U1.9, U3.8
PROC_LPUART1_RTS: U1.11, U3.10
PROC_LPUART1_RX: U1.19, U3.9
PROC_LPUART1_TX: U1.6, U3.7
PROC_SYS_SWCLK: R9.1, U1.17, U2.4
PROC_SYS_SWDIO: R10.1, U1.16, U2.2
RST_OUT_U2_JTAG_RST_B: R8.1, U2.10, U12.1
VCC_S1_6V9: C16.1, C17.1, C21.1, C22.1, J1.1, U8.5, U8.8
VCC_TIER1_3V3: C1.1, C2.1, C3.1, C4.1, C5.1, C8.1, C9.1, C13.1, C14.1, C15.1, C18.1, C19.1, C20.1, C23.1, C24.1, F1.2, I1.2, R1.2, R3.2, R4.2, R5.2, R6.2, R8.2, R9.2, R10.2, R12.2, R13.2, R14.2, R15.1, R17.2, R18.2, R20.1, U1.13, U2.1, U3.6, U5.5, U6.4, U7.4, U8.1, U9.6, U12.5, U13.5
